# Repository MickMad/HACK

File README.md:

#HACK
##HackAday Cortex Kit

A Cortex-M0+ development kit with an Atmel SAM R21, a USB device/host port, a regulator, some passives, a programming header, and breakout headers.

```
Copyright © Michele Perla 2015

This documentation describes Open Hardware and is licensed under the CERN OHL v. 1.2.
You may redistribute and modify this documentation under the terms of the CERN OHL v.1.2. 
(http://ohwr.org/cernohl). This documentation is distributed
WITHOUT ANY EXPRESS OR IMPLIED WARRANTY, INCLUDING OF
MERCHANTABILITY, SATISFACTORY QUALITY AND FITNESS FOR A
PARTICULAR PURPOSE. Please see the CERN OHL v.1.2 for applicable
conditions
```

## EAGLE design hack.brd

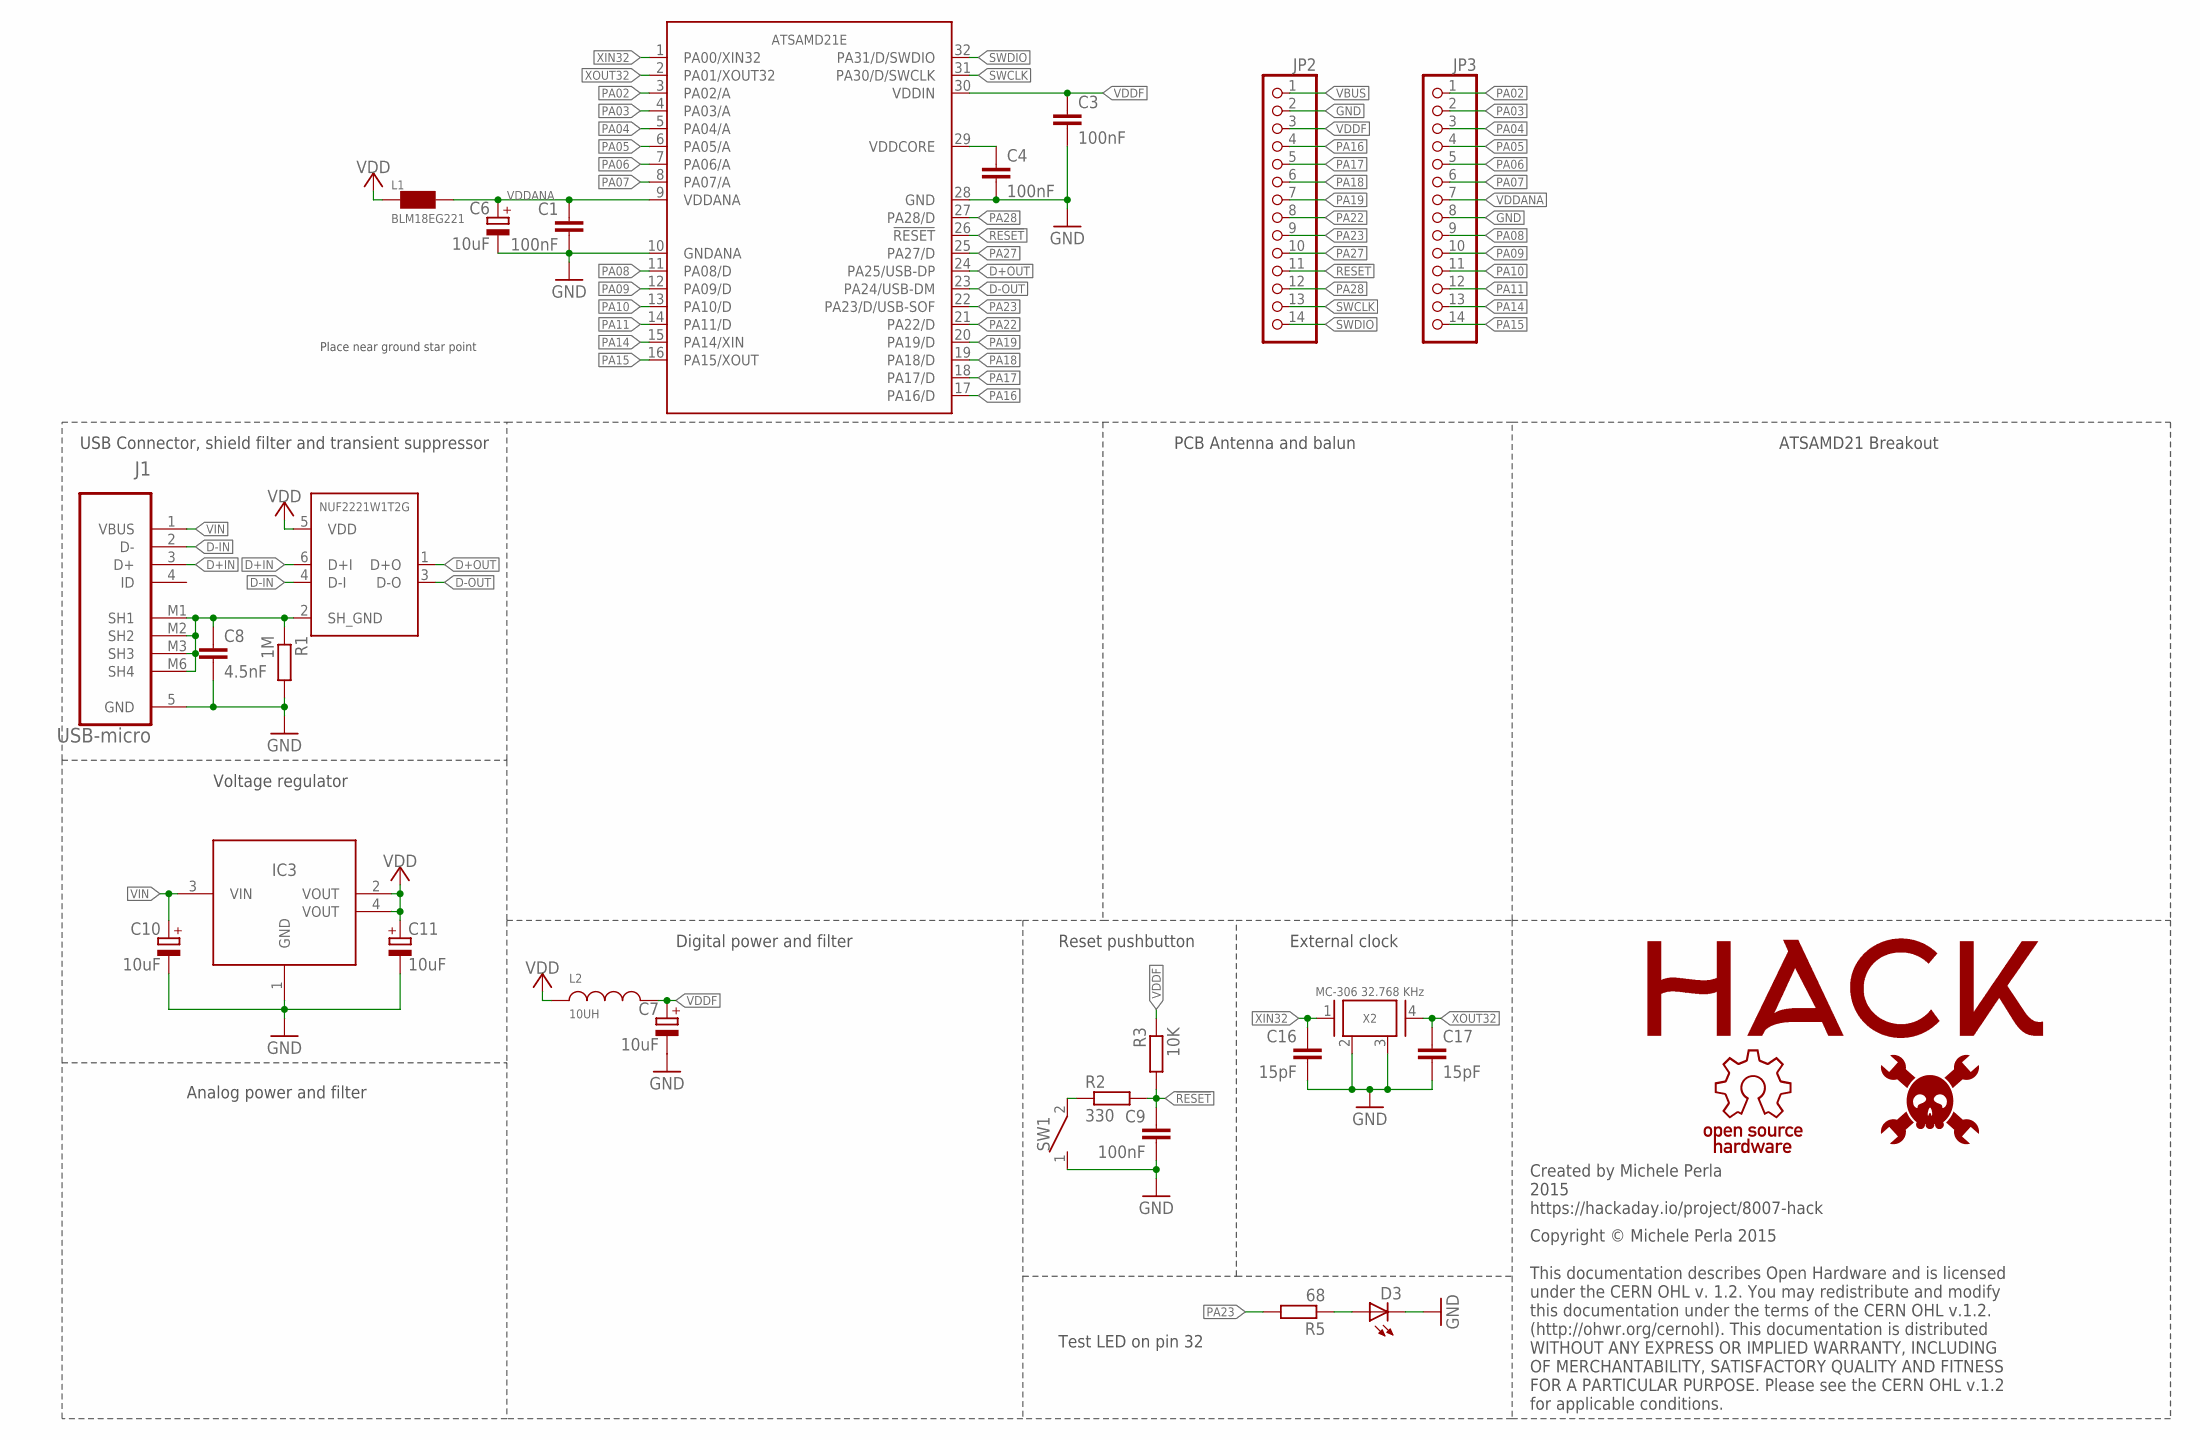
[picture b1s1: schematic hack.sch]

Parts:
C1, C3, C4, C9: 100nF; C0402
C6, C7, C10, C11: 10uF; CT3216
C8: 4.5nF; C0402
C16, C17: 15pF; C0402
D3: LED; LED-0603
IC1: NUF2221W1T2G; SOT-363
IC3: LDO; SOT-223-3
J1: USB-micro; MOLEX_47346-0001
JP2, JP3: PINHD-1X14; 1X14
L1: BLM18EG221; 0603
L2: 10UH; IND_ELLVXG
LOGO1: HACK-LOGO
R1: 1M; R0603
R2: 330; R0603
R3: 10K; R0603
R5: 68; R0603
SW1: SPST3.5X6MM; SWITCH-SMD-3.5X6MM
U1: ATSAMD21E; TQFP32
U$5: HAD-LOGO
U$6: OSHW-LOGO
X2: MC-306 32.768 KHz; MC-306

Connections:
!RESET: C9.1, JP2.11, R2.2, R3.2, U1.26 (!RESET)
D+IN: IC1.6 (D+I), J1.3 (D+)
D+OUT: IC1.1 (D+O), U1.24 (PA25/USB-DP)
D-IN: IC1.4 (D-I), J1.2 (D-)
D-OUT: IC1.3 (D-O), U1.23 (PA24/USB-DM)
GND: C1.2, C3.2, C4.2, C6.-, C7.-, C8.2, C9.2, C10.-, C11.-, C16.2, C17.2, D3.C, IC3.1 (GND), J1.5 (GND), JP2.2, JP3.8, R1.2, SW1.1, U1.10 (GNDANA), U1.28 (GND), X2.2 (GND), X2.3 (GND)
unnamed: D3.A, R5.1
unnamed: C4.1, U1.29 (VDDCORE)
unnamed: R2.1, SW1.2
PA02: JP3.1, U1.3 (PA02/A)
PA03: JP3.2, U1.4 (PA03/A)
PA04: JP3.3, U1.5 (PA04/A)
PA05: JP3.4, U1.6 (PA05/A)
PA06: JP3.5, U1.7 (PA06/A)
PA07: JP3.6, U1.8 (PA07/A)
PA08: JP3.9, U1.11 (PA08/D)
PA09: JP3.10, U1.12 (PA09/D)
PA10: JP3.11, U1.13 (PA10/D)
PA11: JP3.12, U1.14 (PA11/D)
PA14: JP3.13, U1.15 (PA14/XIN)
PA15: JP3.14, U1.16 (PA15/XOUT)
PA16: JP2.4, U1.17 (PA16/D)
PA17: JP2.5, U1.18 (PA17/D)
PA18: JP2.6, U1.19 (PA18/D)
PA19: JP2.7, U1.20 (PA19/D)
PA22: JP2.8, U1.21 (PA22/D)
PA23: JP2.9, R5.2, U1.22 (PA23/D/USB-SOF)
PA27: JP2.10, U1.25 (PA27/D)
PA28: JP2.12, U1.27 (PA28/D)
SH_GND: C8.1, IC1.2 (SH_GND), J1.M1 (SH1), J1.M2 (SH2), J1.M3 (SH3), J1.M6 (SH4), R1.1
SWCLK: JP2.13, U1.31 (PA30/D/SWCLK)
SWDIO: JP2.14, U1.32 (PA31/D/SWDIO)
VBUS: JP2.1
VDD: C11.+, IC1.5 (VDD), IC3.2 (VOUT), IC3.4 (VOUT), L1.1, L2.2
VDDANA: C1.1, C6.+, JP3.7, L1.2, U1.9 (VDDANA)
VDDF: C3.1, C7.+, JP2.3, L2.1, R3.1, U1.30 (VDDIN)
VIN: C10.+, IC3.3 (VIN), J1.1 (VBUS)
XIN32: C16.1, U1.1 (PA00/XIN32), X2.1
XOUT32: C17.1, U1.2 (PA01/XOUT32), X2.4

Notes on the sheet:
USB Connector, shield filter and transient suppressor
Voltage regulator
Analog power and filter
Digital power and filter
Reset pushbutton
External clock
ATSAMD21 Breakout
Created by Michele Perla 2015 https://hackaday.io/project/8007-hack
Test LED on pin 32
Copyright © Michele Perla 2015 This documentation describes Open Hardware and is licensed under the CERN OHL v. 1.2. You may redistribute and modify this documentation under the terms of the CERN OHL v.1.2. (http://ohwr.org/cernohl). This documentation is distributed WITHOUT ANY EXPRESS OR IMPLIED 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
PCB Antenna and balun
Place near ground star point

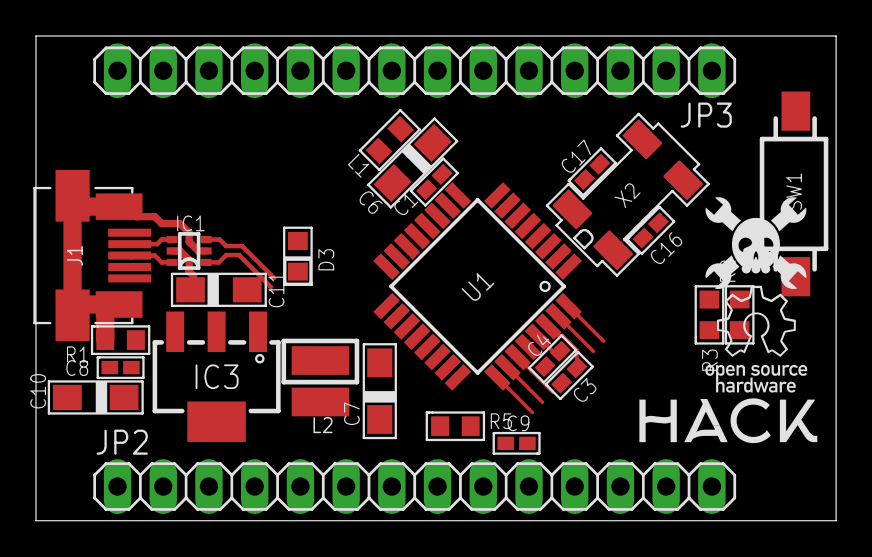
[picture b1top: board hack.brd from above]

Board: 2 copper layers, 44.5 x 26.9 mm, 29 parts (0 on the bottom side), 38 nets.

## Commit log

2015-08-31 :neckbeard: Added .gitattributes & .gitignore files
2015-10-05 Second commit
2015-10-08 Finishing layout, added PCB antenna
2015-10-12 Third commit
    Changed cutout of PCB so that one side hosts the antenna; moved part of
    the header to the right side (use a female receptacle instead of a male
    header to retain breadboard usability)
2015-10-12 Added temp EAGLE CAD files to .gitignore
2015-10-12 Added impedance controlled microstrips
    Added impedance controlled microstrips (diff. impedance of 100 Ohms from
    chip to balun, single ended impedance of 50 Ohms from balun to antenna)
2015-10-13 1st revision board is done
2015-10-14 3D model added
    It's missing the balun and the 32.768 KHz crystal models only
2015-12-21 Migrating project to KiCAD
2015-12-23 Final components placement almost done
    During this phase I checked if everything could fit in the board. It
    didn't, so I found a replacement LDO (in a small 1.2x1.2mm DFN package)
    that needs 2x0603 ceramic caps rather than two clunky electros (more
    free space then) and I finally changed the D21E package to QFN as well,
    now everything seems to fit quite well.
2015-12-24 Layout 99,9% finished
    Nets 100% routed, need to double check if copper pours are all connected
    to ground; added fiducials on board (for pick-n-place machines), I only
    need to find a good spot for them
2015-12-28 Cleaning up before test run
    Removed obsolete Eagle CAD files, added OSHW/Hackaday logos on schematic
    and silkscreen, removed ground connections for pins 2-3 of 32.768 KHz
    XTAL, removed traces under USB data lines, moving analog lines around
    (not beneath) XTAL (w.i.p.), moved components names on silkscreen to be
    readable, set fiducials in position, fixed SPST SMD package
2015-12-29 Layout 100% completed, cosmetics not yet
2016-01-04 Finished silkscreen cosmetics, added gerbers
2016-01-05 Added castellated pins
2016-01-05 Fixed gerbers (silkcreen issue with one pin)
2016-01-05 Changed USB connector package, revised layout
2016-01-05 Updated GERBER files, removed DRC errors in PCB
2016-01-05 fresh PDF and Gerbers in separate folders. Step/VRML files ready for 3D render
2016-01-06 FreeCAD 3D render in Fabricate dir, moved gerber dir nested under kicad
2016-01-06 Added datasheets, manufacturer numbers field for every component
2016-01-06 Updated KiCost BOM file w manf# field
2016-01-06 Added pin header datasheet+manf# (15 pins instead of 13 because 15 is cheaper)
2016-01-07 added 3d model for ELL-VFG and some other minor edits
2016-01-07 Added Seeedstudio costs for some components in schematic, changed 2.2uF manf# field to real manufacturer number instead of Seeedstudio SKU
2016-01-07 Updated Seeedstudio cost information
2016-01-07 Fixed KiCost BOM issue, updated BOM
2016-01-07 Updated BOM, added sheet fixed for 20 boards
    Usefult for test run purposes
2016-01-07 Updated BOM
2016-01-08 Added secondary USB connector footprint
    Previous one is only available from Seeedstudio, this one is from FCI
    and available from all distributors
2016-01-08 Changed LED, headers, USBmicro, XTAL manf#
    These parts are readily available from all distributors, previous ones
    were only sold by Seeed
2016-01-08 Updated BOMs
    One contains normally available parts numbers (hack-Digi-BOM), the other
    contains mostly Seeedstudio-sourced parts numbers (hack-Seeed-BOM)
2016-01-18 Optimized footprints, freed some PCB real estate
2016-01-18 Updated fabrication files
2016-01-18 Updated BOM (re-runned KiCost to check today's price)
2016-01-18 Fixed gerbers (outline was in all layers)
2016-01-18 Fixed PCB (not connected LED ground), updated fab files accordingly
2016-01-18 Updated pcb+gerber (via was still missing from D1 to GND)
2016-01-18 fresh gerber and seeed BoM for ready for prototype
2016-01-19 added Freecad 3d model for ELL-VFG inductor
2016-01-20 Added VBUS pin, GND pin near VDDANA
2016-01-21 test commit
2016-01-21 Reducing board size (w.i.p.)
2016-01-22 Reduced overall board size
2016-01-22 Fixed footprints refereneces on top silkscreen
2016-01-22 Added back gerber files zip
2016-01-25 Form factor is PDIP-24 now, ready to fab
    HACK now fits a PDIP-24 package (its solderable thru-hole headers
    spacing is now 0.6"); being longer there's some space on the top side,
    so it now features a convenient Cortex SWD Connector, a 2x5 male pin
    header with 50 mils spacing in SMD package.
2016-01-28 fresh 3D model and graphics
2016-03-22 new 3D models from Maurice with open source license
2016-07-13 Add 1-click-bom and kitnic.yaml
2016-08-13 Change image links to be relative to repo root
